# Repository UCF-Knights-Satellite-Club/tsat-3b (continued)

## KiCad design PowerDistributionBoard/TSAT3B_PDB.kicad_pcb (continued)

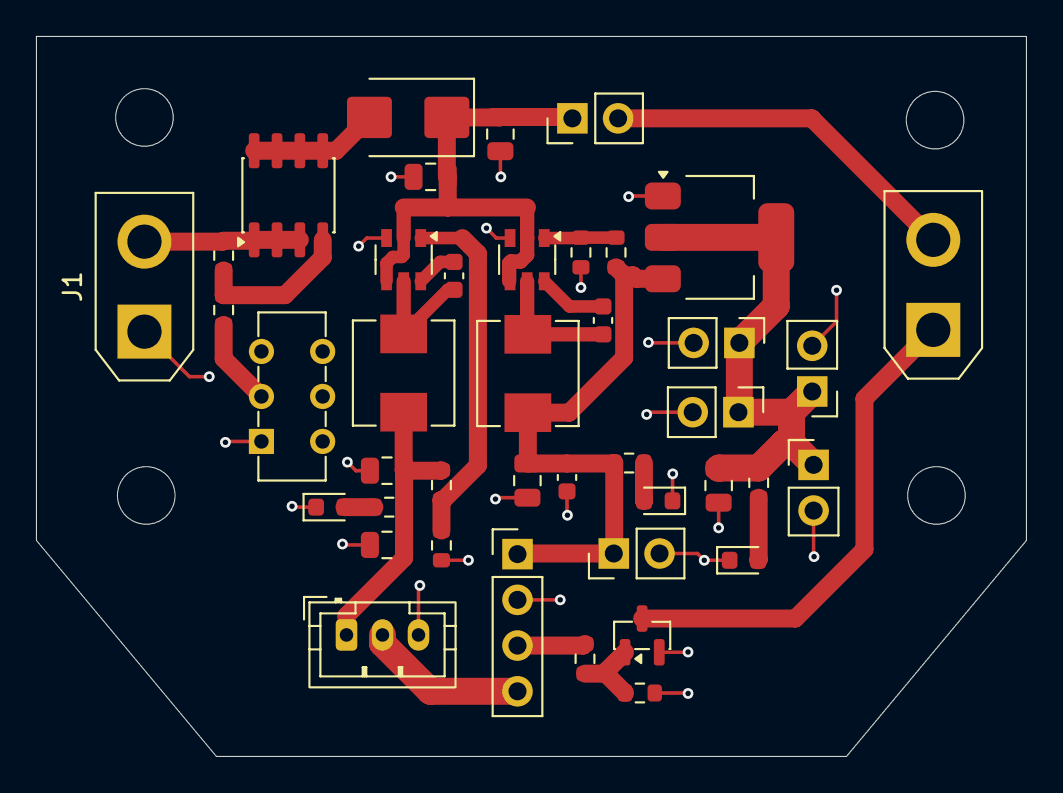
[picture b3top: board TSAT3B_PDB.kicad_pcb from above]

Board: 2 copper layers, 55.0 x 40.0 mm, 42 parts (0 on the bottom side), 23 nets.

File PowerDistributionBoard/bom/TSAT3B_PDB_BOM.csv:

"Reference","Value","Footprint","MPN","Manufacturer","Qty"
"C1,C2,C4,C6-C8","22u / 25V","Capacitor_SMD:C_0805_2012Metric","TCC0805X5R226M250FT","CCTC","6"
"C3,C5,C9","100n / 50V","Capacitor_SMD:C_0603_1608Metric","0603B104K500NT","FH","3"
"D1","SS54SMB","Diode_SMD:D_SMB","SS54SMB","BORN","1"
"D2-D4","GREEN","LED_SMD:LED_0603_1608Metric","YLED0603G","YONGYUTAI","3"
"J1","BATTERY","TSAT3B:AMASS_XT30UPB-M_P1_Positive","XT30UPB-M","","1"
"J2","ARM LINK","Connector_PinHeader_2.54mm:PinHeader_1x02_P2.54mm_Vertical","PZ254V-11-02P","","1"
"J3","PICO","Connector_PinHeader_2.54mm:PinHeader_1x02_P2.54mm_Vertical","PZ254V-11-02P","","1"
"J4","LoRa","Connector_PinHeader_2.54mm:PinHeader_1x02_P2.54mm_Vertical","PZ254V-11-02P","","1"
"J5","GPS","Connector_PinHeader_2.54mm:PinHeader_1x02_P2.54mm_Vertical","PZ254V-11-02P","","1"
"J6","IMU","Connector_PinHeader_2.54mm:PinHeader_1x02_P2.54mm_Vertical","PZ254V-11-02P","","1"
"J7","SD CARD","Connector_PinHeader_2.54mm:PinHeader_1x02_P2.54mm_Vertical","PZ254V-11-02P","","1"
"J8","SERVO 1","Connector_JST:JST_PH_B3B-PH-K_1x03_P2.00mm_Vertical","2.54-1*3P","","1"
"J9","Conn_01x04","Connector_PinHeader_2.54mm:PinHeader_1x04_P2.54mm_Vertical","","","1"
"J11","CUTTER 1","TSAT3B:AMASS_XT30UPB-M_P1_Positive","XT30UPB-M","","1"
"L1,L2","2.2uH","TSAT3B:L_TDK_SPM5030VT","SPM5030VT-2R2M-D","TDK","2"
"Q1","AO3400A","Package_TO_SOT_SMD:SOT-23","AO3400A","Alpha & Omega Semiconductor","1"
"Q3","AO4407A","Package_SO:SOIC-8_3.9x4.9mm_P1.27mm","AO4407A","Alpha & Omega Semiconductor","1"
"R1,R3","73.2k","Resistor_SMD:R_0603_1608Metric","0603WAF7322T5E","","2"
"R2,R9,R12","10k","Resistor_SMD:R_0603_1608Metric","CRGCQ0603F10K","TE Connectivity","3"
"R4","8.2k","Resistor_SMD:R_0603_1608Metric","FRQ0603F8201TS","","1"
"R5-R7,R13","1k","Resistor_SMD:R_0603_1608Metric","1RC0603F1001","","4"
"R8","100R","Resistor_SMD:R_0603_1608Metric","CR0603JA0101G","","1"
"SW1","MSS22D18G2","TSAT3B:SW_SHOUHAN_MSS22D18G2","MSS22D18G2","SHOU HAN","1"
"U1,U2","SY8105IADC","TSAT3B:SY8105IADC_TSOT23_6_MfrLand","SY8105IADC","Silergy Corp","2"
"U3","TLV1117LV33","Package_TO_SOT_SMD:SOT-223-3_TabPin2","TLV1117LV33DCYR","Texas Instruments","1"
